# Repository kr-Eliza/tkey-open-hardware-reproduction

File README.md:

<p align="center">
<picture>
  <source media="(prefers-color-scheme: light)" srcset=".github/assets/banner-light.svg">
  
</picture>
</p>

<p align="center">
  <i>Can a student team rebuild an open hardware security key from its public sources, make it work, and understand what it takes to trust it?</i><br>
  We reproduced the <a href="https://tillitis.se">Tillitis TKey</a>: a 2-layer, hand-solderable redesign of its PCB, assembled in the lab and brought up until it behaved like a standard TKey.
</p>

<p align="center"><sub>Student project at my engineering school's LabCyber, team of six, November 2025 to April 2026 (<a href="https://ptcc.fr/lab-cyber/les-projets-du-labcyber/reproduction-dune-cle-dauthentification-open-hardware/">project page on the LabCyber site</a>). The project <a href="https://ptcc.fr/lab-cyber/les-projets-du-labcyber/projets-etudiants-au-labcyber/">continues at the LabCyber in 2026-2027</a>.</sub></p>

<p align="center">
<picture>
  <source media="(prefers-color-scheme: light)" srcset=".github/assets/divider-light.svg">
  
</picture>
</p>

<p align="center">
<picture>
  <source media="(prefers-color-scheme: light)" srcset=".github/assets/stats-light.svg">
  
</picture>
</p>

<h3>
<picture>
  <source media="(prefers-color-scheme: light)" srcset=".github/assets/h-why-this-project-light.svg">
  
</picture>
</h3>

Most hardware security keys are closed: their schematics, firmware and key storage cannot be inspected, so users have to trust the vendor. The TKey takes the opposite approach. Its hardware (a Lattice iCE40UP5K FPGA running a small RISC-V core, plus a CH552 USB controller) and its firmware are fully open, which makes it a good subject for a reproduction and hardening project:

- **reproduce** a real security device from its open sources, with the tools and constraints of a school lab;
- **understand** how it generates and protects its secrets;
- **propose** ways to strengthen it, and document everything as reusable material for the LabCyber.

**My part**, with one teammate: the custom PCB route, from the KiCad redesign to the order, the assembly and the bring-up of the board. The other members worked on the reference key, the Voltera prototype, the security analysis and the project management.

<h3>
<picture>
  <source media="(prefers-color-scheme: light)" srcset=".github/assets/h-three-routes-to-a-tkey-light.svg">
  
</picture>
</h3>

<p align="center">
<picture>
  <source media="(prefers-color-scheme: light)" srcset=".github/assets/journey-light.svg">
  
</picture>
</p>

| Route | What it is | Outcome |
|-------|-----------|---------|
| Reference key | a pre-assembled TKey Unlocked from Tillitis, provisioned by us | provisioned and used for signing, SSH and login MFA |
| Custom PCB | our 2-layer redesign, ordered from a PCB maker, assembled in the lab | assembled, powered and brought up until it behaved like a standard TKey |
| Voltera V-One | the same design printed in house with conductive ink | traces printed, assembly stopped (wrong consumables) |

<h3>
<picture>
  <source media="(prefers-color-scheme: light)" srcset=".github/assets/h-the-reference-tkey-light.svg">
  
</picture>
</h3>

The TKey Unlocked ships with a blank FPGA: no bitstream, no Unique Device Secret (UDS). We provisioned it ourselves from the `TK1-24.03` release of [tillitis-key1](https://github.com/tillitis/tillitis-key1):

1. **secrets**: the Tillitis provisioning tool derives the UDS from user entropy and 256 random bytes (HKDF);
2. **bitstream**: Yosys (synthesis), nextpnr-ice40 (place and route), the RISC-V cross-compiler for the firmware, icepack, about 102 KB in the end;
3. **flashing**: `tillitis-iceprog` through the TP-1 programmer, read back with `VERIFY OK`, then the UDS files were deleted from disk.

The provisioned key was then used for three things:

- **file signing** with `tkey-sign` (Ed25519), the key waiting for a physical touch before signing;
- **SSH** with `tkey-ssh-agent`, from Windows and Linux, no password, impossible once the key is unplugged;
- **two-factor login** on a Linux desktop: PAM asks for the password and a TKey challenge-response at the LightDM greeter.

<h3>
<picture>
  <source media="(prefers-color-scheme: light)" srcset=".github/assets/h-redesigning-the-pcb-light.svg">
  
</picture>
</h3>

The original TKey is a tiny 4-layer board with 0402 parts. We redesigned it in KiCad 9 for what a school lab can build and solder by hand.

| | Original TK1 | Our version |
|---|---|---|
| Layers | 4 | 2 |
| Board | USB stick | 57.6 x 39.8 mm card |
| Passives | 0402 / 0603 | 0805 |
| SPI flash | W25Q80 (USON-8) | SST25VF080B (SOIC-8) |
| USB connector | USB-A plug | USB-C receptacle (GCT USB4085) |
| Status LED | one RGB LED | three discrete 0805 LEDs |
| User input | capacitive touch sensor | push button on the same `TOUCH_EVENT` signal |
| Flash `WP#` / `HOLD#` | tied to fixed levels | routed to spare FPGA pins, so firmware can control write protection |
| Regulators | parts no longer available | NCP752 (3.3 V), MCP1824 (2.5 V), NCV8164 (1.2 V) |

Going from 4 to 2 layers removes the internal ground and power planes, so we had to work around it:

- copper ground pours on both layers, stitched with vias, to rebuild an approximate ground plane;
- decoupling capacitors as close as possible to every power pin, especially around the FPGA and the CH552;
- the USB D+ / D- pair kept short, tightly coupled and surrounded by ground, since a true 90 Ω impedance is hard to guarantee without a reference plane.

<table>
  <tr>
    <td></td>
    <td></td>
  </tr>
  <tr>
    <td align="center"><sub>front copper</sub></td>
    <td align="center"><sub>back copper</sub></td>
  </tr>
</table>

The 20 test points of the original are kept on the back (SPI, UART, GPIO and every supply rail), which is what made the bring-up possible.

The full bill of materials is in [`hardware/tk1-2layer/bom.csv`](hardware/tk1-2layer/bom.csv) and the schematic in [`docs/schematic-2layer.pdf`](docs/schematic-2layer.pdf).

<h3>
<picture>
  <source media="(prefers-color-scheme: light)" srcset=".github/assets/h-assembly-and-bring-up-light.svg">
  
</picture>
</h3>

The boards were made by an external PCB maker (2-layer FR4, 1.6 mm) and assembled in the lab: stencil and lead-free solder paste, pick-and-place for the passives, reflow oven, then inspection under the microscope. Two LEDs had been placed backwards and one CH552 pad lacked solder: all three were reworked by hand.

<table>
  <tr>
    <td width="33%"></td>
    <td width="33%"></td>
    <td width="33%"></td>
  </tr>
  <tr>
    <td align="center"><sub>assembled</sub></td>
    <td align="center"><sub>powered</sub></td>
    <td align="center"><sub>wired to the test points</sub></td>
  </tr>
</table>

**First power-on**, through a current-limited supply (100 mA): the 2.5 V, 1.2 V and 3.3 V rails were all within ±2 % of their targets, with about 15 mA drawn at idle and no short.

**Bring-up** was the hardest part. The board enumerated on Linux as `/dev/ttyACM0`, but `tkey-sign` failed with `GetAppNameVersion: ReadFrame: Read timeout`.

<p align="center">
<picture>
  <source media="(prefers-color-scheme: light)" srcset=".github/assets/bringup-light.svg">
  
</picture>
</p>

- Reflashing the official FPGA image through the TP-1 passed verification but did not change anything.
- The fix was on the **CH552 USB controller**: we rebuilt its firmware with `sdcc`, flashed it with `chprog`, and entered its bootloader by hand with a 10 kΩ pull-up on D+, since we had no dedicated reset adapter.
- From then on, the reproduced board behaved like a standard TKey.

<h3>
<picture>
  <source media="(prefers-color-scheme: light)" srcset=".github/assets/h-voltera-prototype-light.svg">
  
</picture>
</h3>

In parallel, another part of the team printed the design in house with a Voltera V-One: silver conductive ink for the traces, a drilling head and rivets for the vias, then solder paste and reflow on the heated bed. A board takes about an hour, which makes it a good tool to check a routing or a footprint quickly.

<table>
  <tr>
    <td width="45%"></td>
    <td width="55%"></td>
  </tr>
  <tr>
    <td align="center"><sub>printed board</sub></td>
    <td align="center"><sub>layout adapted for the printer</sub></td>
  </tr>
</table>

The traces printed well, but the assembly was stopped: the cartridge and nozzle available were not the right ones for solder paste. With the 0.5 mm pitch of the FPGA, the paste deposits would also have needed careful tuning to avoid bridges. Our conclusion: very good for testing, not for producing this board.

<h3>
<picture>
  <source media="(prefers-color-scheme: light)" srcset=".github/assets/h-supply-chain-light.svg">
  
</picture>
</h3>

A security key is only as trustworthy as the way it is built, so we started documenting the software supply chain, in [`supply-chain/`](supply-chain):

- [`sbom.cdx.json`](supply-chain/sbom.cdx.json): a CycloneDX 1.6 SBOM of the `tillitis-key1` sources, generated with syft (287 components);
- [`pbom.json`](supply-chain/pbom.json): the build provenance of the CH552 firmware (source commit, `tkey-builder` toolchain image, build command, SHA-256 of the produced `.hex` and `.bin`);
- [`hashes.txt`](supply-chain/hashes.txt): the same hashes, so anyone can rebuild the firmware and compare.

Built FPGA images are **not** published here: a TKey bitstream built for SPI flash can embed the device secrets (UDS), so it should never leave the bench it was made on.

<h3>
<picture>
  <source media="(prefers-color-scheme: light)" srcset=".github/assets/h-security-proposals-light.svg">
  
</picture>
</h3>

These are proposals only. For lack of time within the project, they could not be studied in depth: none of them was implemented in firmware or tested, and the reflection would need to go further before any of them is applied.

- **Memory isolation.** We studied a published out-of-bounds read in the TKey application RAM (a time-of-check to time-of-use bug on the size of the message to sign). Tillitis fixed it in the `TK1-24.03` hardware release, which is the one we built.
- **Post-quantum signatures.** Ed25519 would not resist a large quantum computer. We proposed a hybrid scheme, Ed25519 plus ML-DSA (FIPS 204), so a signature stays valid as long as one of the two holds.
- **Flash write protection.** Routing `WP#` and `HOLD#` to the FPGA gives the firmware a way to lock the flash, which the original board does not offer. The pins are routed on our board, but no firmware uses them yet.

The redesign also has a cost for security, worth keeping in mind for a hardened version: a larger board, exposed test points and a flash in a package that is easy to probe or swap are all easier to attack than the original stick. This is fine for a lab and teaching board, not for a key carried in a pocket.

<h3>
<picture>
  <source media="(prefers-color-scheme: light)" srcset=".github/assets/h-repository-light.svg">
  
</picture>
</h3>

```
hardware/
  tk1-2layer/          final 2-layer board sent to fabrication (KiCad 9 project, libraries, 3D models, BOM)
  voltera-prototype/   last version adapted for the Voltera V-One
docs/
  schematic-2layer.pdf
  images/              photos, KiCad renders, demo GIFs
supply-chain/          SBOM, build provenance and hashes of the CH552 firmware
```

Open `hardware/tk1-2layer/tk1-0805.kicad_pro` in KiCad 9. Only the last version of each board is kept; the FPGA design and firmware are the unmodified ones from [tillitis-key1](https://github.com/tillitis/tillitis-key1).

<h3>
<picture>
  <source media="(prefers-color-scheme: light)" srcset=".github/assets/h-limits-and-next-steps-light.svg">
  
</picture>
</h3>

- The USB signal quality on 2 layers was not measured; the board works, but its margin is unknown.
- Long-term reliability and repeatability over several boards remain to be tested.
- The reproduced board is programmed through its SPI flash, the development path: it is not locked like a production key (NVCM).
- The Voltera assembly still has to be validated with the right consumables.
- The security proposals are only first ideas: time ran out before they could be studied in depth, implemented in firmware or tested. This is where the 2026-2027 LabCyber project picks up (see below).

<h3>
<picture>
  <source media="(prefers-color-scheme: light)" srcset=".github/assets/h-the-project-continues-light.svg">
  
</picture>
</h3>

Our project is presented on the LabCyber site: [Reproduction d'une clé d'authentification open hardware](https://ptcc.fr/lab-cyber/les-projets-du-labcyber/reproduction-dune-cle-dauthentification-open-hardware/).

This work goes on at the LabCyber in 2026-2027, as one of its [student projects](https://ptcc.fr/lab-cyber/les-projets-du-labcyber/projets-etudiants-au-labcyber/): *reproduction and hardening of an open hardware device for authentication or data storage*, with the TKey and WooKey-type devices as examples. It starts where we stopped: understand the device, rebuild it from its open sources, harden it (firmware, manufacturing chain, attestation), and publish the results as commons that anyone can reuse.

**About the LabCyber.** The [LabCyber](https://ptcc.fr/lab-cyber/) is a shared lab of the Campus Cyber, operated by Inria within the [PTCC](https://ptcc.fr/programme-de-transfert-au-campus-cyber/qui-sommes-nous/) (Programme de Transfert au Campus Cyber, funded by France 2030). It brings together a fab lab, a cyber range and a data hub, hosts student teams for end-of-studies projects in hardware cybersecurity, and hosted this project. Its equipment includes:

- PCB fabrication and assembly: milling machine, reflow oven, soldering and hot-air stations, PCB microscope;
- electronics analysis: oscilloscope, logic analyzer, function generator, Faraday cage, software-defined radio;
- a cyber range to simulate IT and OT systems, and a contribution to the *Studio des Communs de la cybersécurité*.

<h3>
<picture>
  <source media="(prefers-color-scheme: light)" srcset=".github/assets/h-credits-and-license-light.svg">
  
</picture>
</h3>

Team of six engineering students, mentored at the LabCyber by two members of the PTCC, including [@Acathla-fr](https://github.com/Acathla-fr), who also helped finalize the files sent to fabrication. Original TKey design by [Tillitis AB](https://github.com/tillitis/tk1-pcba).

This is a modified version of the TK1 PCB by Tillitis AB, distributed under the same licence, the **CERN Open Hardware Licence Version 2, Strongly Reciprocal**. See [LICENSE.txt](LICENSE.txt).

```
Copyright Tillitis AB 2022-2024.
Modifications copyright 2026 the Open TKey student team.
This source describes Open Hardware and is licensed under the CERN-OHL-S v2.
You may redistribute and modify this source and make products using it under
the terms of the CERN-OHL-S v2 (https://ohwr.org/cern_ohl_s_v2.txt).
This source is distributed WITHOUT ANY EXPRESS OR IMPLIED WARRANTY,
INCLUDING OF MERCHANTABILITY, SATISFACTORY QUALITY AND FITNESS FOR A
PARTICULAR PURPOSE. Please see the CERN-OHL-S v2 for applicable conditions.
Source location: https://github.com/kr-Eliza/tkey-open-hardware-reproduction
Original source location: https://github.com/tillitis/tk1-pcba
Modified in 2026: 2-layer board, 0805 passives, SOIC-8 flash, USB-C connector,
discrete LEDs, push button, flash WP#/HOLD# routed to the FPGA, replacement
regulators (see "Redesigning the PCB" above).
```

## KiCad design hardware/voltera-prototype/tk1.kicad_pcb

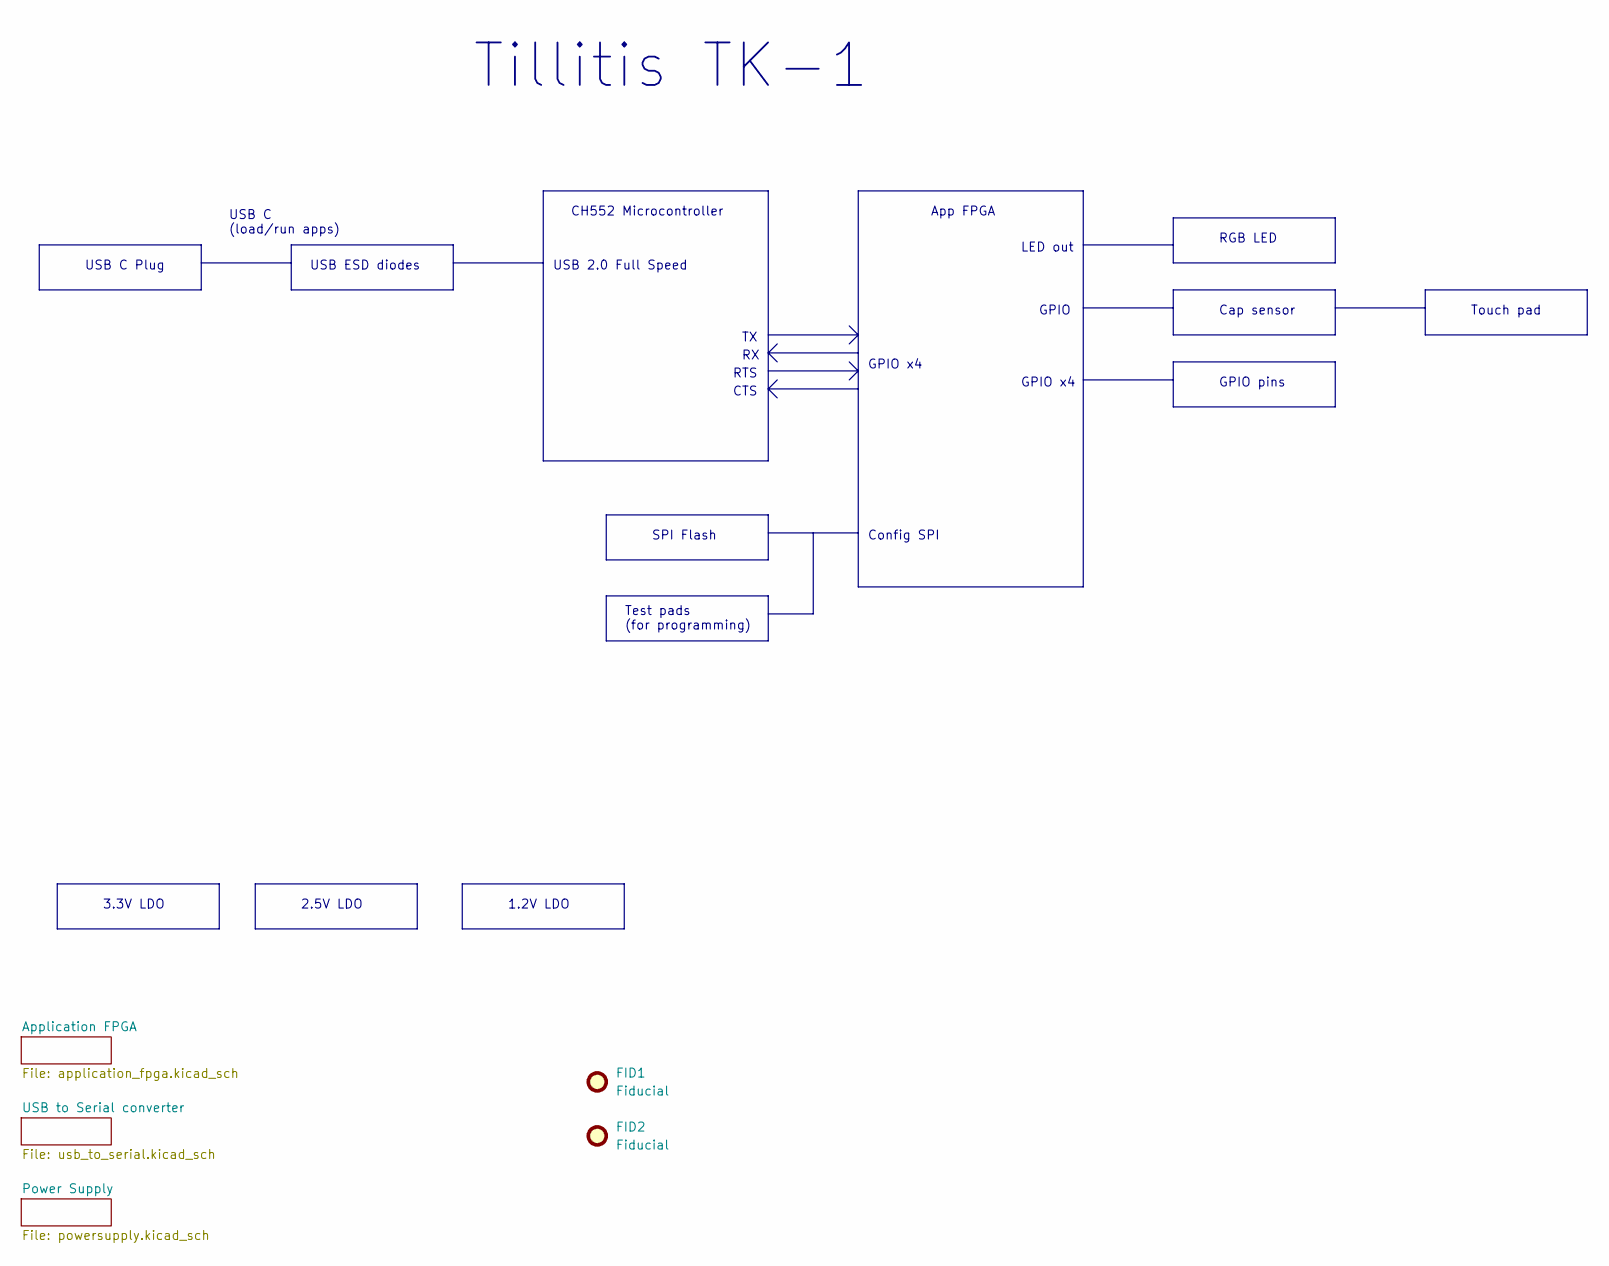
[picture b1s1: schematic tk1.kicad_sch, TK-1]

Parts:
FID1, FID2: Fiducial; Fiducial_0.75mm_Mask1.5mm

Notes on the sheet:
USB ESD diodes
Touch pad
GPIO x4
GPIO pins
Cap sensor
USB 2.0 Full Speed
RTS
USB C Plug
CH552 Microcontroller
RGB LED
USB C (load/run apps)
1.2V LDO
3.3V LDO
CTS
2.5V LDO
App FPGA
Config SPI
Tillitis TK-1
SPI Flash
GPIO
LED out
Test pads (for programming)

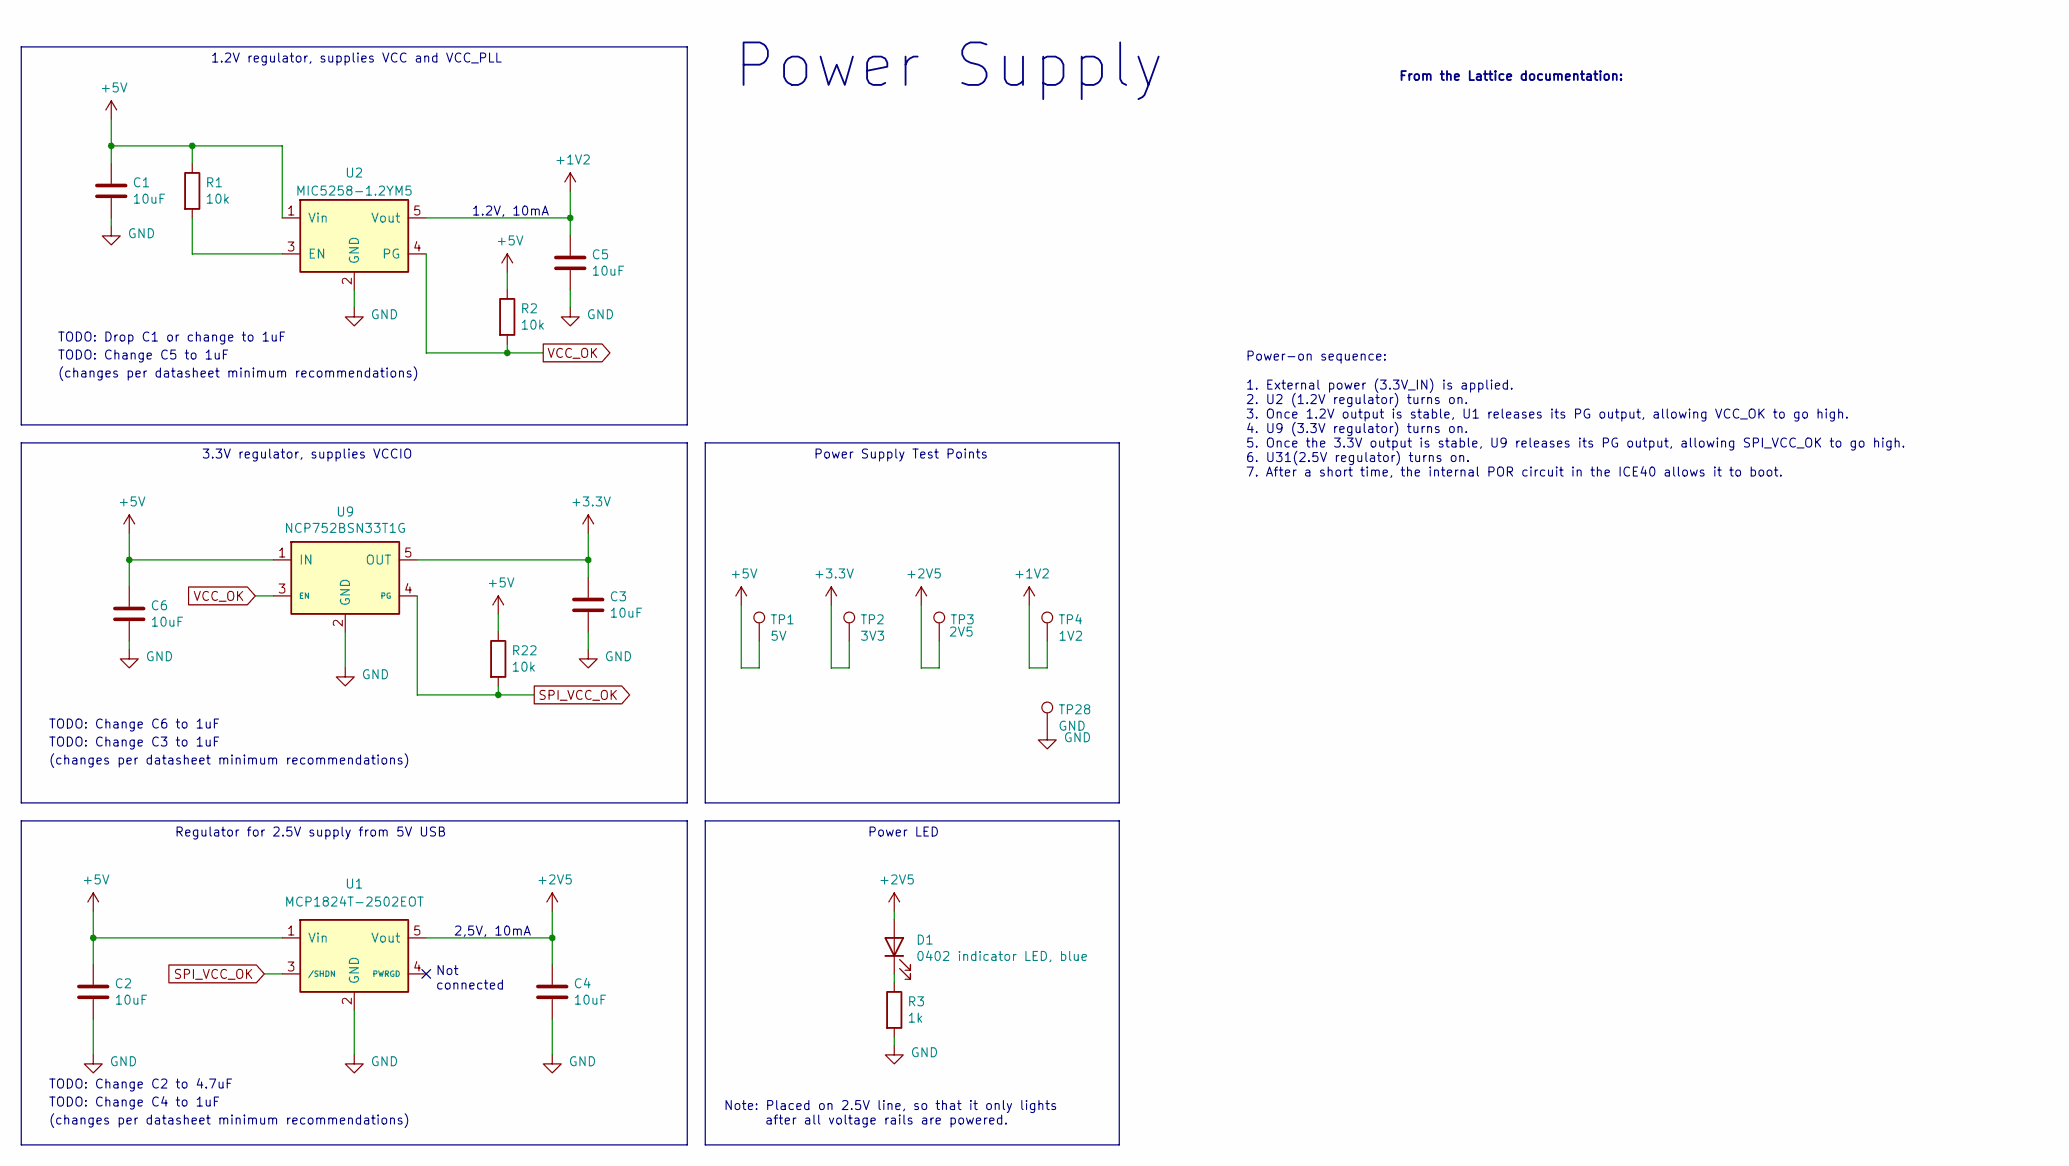
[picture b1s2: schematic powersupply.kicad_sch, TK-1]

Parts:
C1, C2, C3, C4, C5, C6: 10uF; C_0805_2012Metric
D1: 0402 indicator LED, blue; LED_0805_2012Metric; Manufacturer Part Number NCD0402B1
R1, R2, R22: 10k; R_0805_2012Metric
R3: 1k; R_0805_2012Metric
TP1: 5V; TestPoint_Pad_D1.0mm
TP2: 3V3; TestPoint_Pad_D1.0mm
TP3: 2V5; TestPoint_Pad_D1.0mm
TP4: 1V2; TestPoint_Pad_D1.0mm
TP28: GND; TestPoint_Pad_D1.0mm
U1: MCP1824T-2502EOT; SOT-23-5; Manufacturer Part Number MCP1824T-2502EOT
U2: MIC5258-1.2YM5; SOT-23-5; Manufacturer Part Number MIC5258-1.2YM5
U9: NCP752BSN33T1G; Manufacturer Part Number NCP752BSN33T1G

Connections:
+1V2: C5.1, TP4.1, U2.5 (Vout); also elsewhere on the board
+2V5: C4.1, D1.2 (A), TP3.1, U1.5 (Vout); also elsewhere on the board
+3.3V: C3.1, TP2.1, U9.5 (OUT); also elsewhere on the board
+5V: C1.1, C2.1, C6.1, R1.1, R2.1, R22.1, TP1.1, U1.1 (Vin), U2.1 (Vin), U9.1 (IN); also elsewhere on the board
GND: C1.2, C2.2, C3.2, C4.2, C5.2, C6.2, R3.2, TP28.1, U1.2 (GND), U2.2 (GND), U9.2 (GND); also elsewhere on the board
unnamed: D1.1 (K), R3.1
unnamed: R1.2, U2.3 (EN)
SPI_VCC_OK: R22.2, U1.3 (/SHDN), U9.4 (PG)
VCC_OK: R2.2, U2.4 (PG), U9.3 (EN)

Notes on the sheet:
Power-on sequence: 1. External power (3.3V_IN) is applied. 2. U2 (1.2V regulator) turns on. 3. Once 1.2V output is stable, U1 releases its PG output, allowing VCC_OK to go high. 4. U9 (3.3V regulator) turns on. 5. Once the 3.3V output is stable, U9 releases its PG output, allowing SPI_VCC_OK to go 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
TODO: Change C2 to 4.7uF
(changes per datasheet minimum recommendations)
TODO: Change C6 to 1uF
2,5V, 10mA
Note: Placed on 2.5V line, so that it only lights after all voltage rails are powered.
TODO: Change C3 to 1uF
1.2V, 10mA
Power Supply
TODO: Drop C1 or change to 1uF
TODO: Change C5 to 1uF
From the Lattice documentation:
1.2V regulator, supplies VCC and VCC_PLL
3.3V regulator, supplies VCCIO
TODO: Change C4 to 1uF
Not connected
Power Supply Test Points
Power LED
Regulator for 2.5V supply from 5V USB

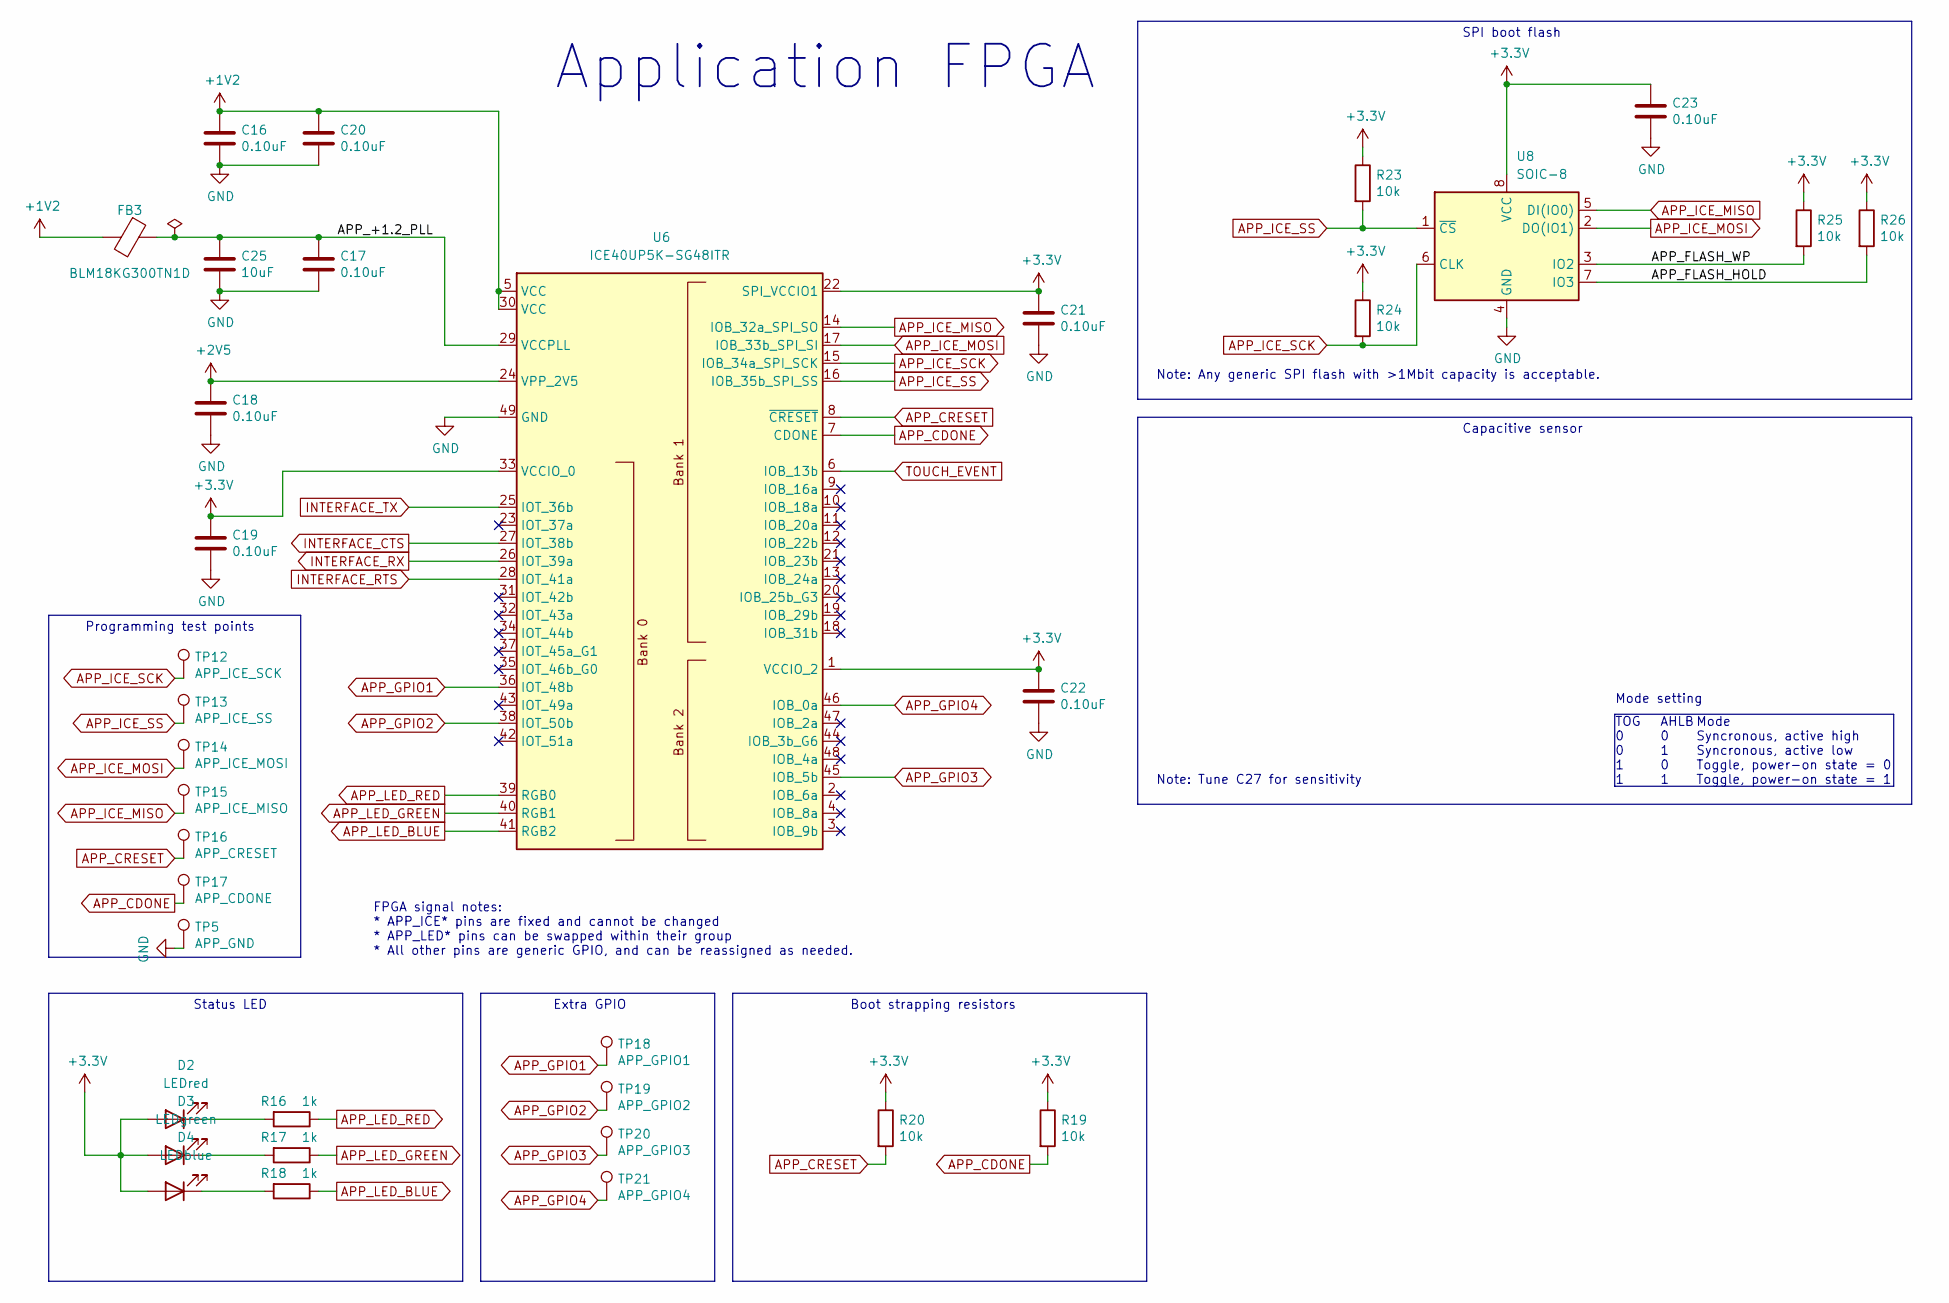
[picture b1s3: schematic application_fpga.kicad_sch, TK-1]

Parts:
C16, C17, C18, C19, C20, C21, C22, C23: 0.10uF; C_0805_2012Metric
C25: 10uF; C_0805_2012Metric
D2: LEDred; LED_0805_2012Metric_Pad1.15x1.40mm_HandSolder
D3: LEDgreen; LED_0805_2012Metric_Pad1.15x1.40mm_HandSolder
D4: LEDblue; LED_0805_2012Metric_Pad1.15x1.40mm_HandSolder
FB3: BLM18KG300TN1D; Ferritbead_0603_1608Metric; Manufacturer Part Number BLM18KG300TN1D
R16, R17, R18: 1k; R_0805_2012Metric
R19, R20, R23, R24, R25, R26: 10k; R_0805_2012Metric
TP5: APP_GND; TestPoint_Pad_D1.0mm
TP12: APP_ICE_SCK; TestPoint_Pad_D1.0mm
TP13: APP_ICE_SS; TestPoint_Pad_D1.0mm
TP14: APP_ICE_MOSI; TestPoint_Pad_D1.0mm
TP15: APP_ICE_MISO; TestPoint_Pad_D1.0mm
TP16: APP_CRESET; TestPoint_Pad_D1.0mm
TP17: APP_CDONE; TestPoint_Pad_D1.0mm
TP18: APP_GPIO1; TestPoint_Pad_D1.0mm
TP19: APP_GPIO2; TestPoint_Pad_D1.0mm
TP20: APP_GPIO3; TestPoint_Pad_D1.0mm
TP21: APP_GPIO4; TestPoint_Pad_D1.0mm
U6: ICE40UP5K-SG48ITR; QFN-48-1EP_7x7mm_P0.5mm_EP5.6x5.6mm; Manufacturer Part Number ICE40UP5K-SG48ITR
U8: SOIC-8; SOIC-8_3.9x4.9mm_P1.27mm; Manufacturer Part Number W25Q80DVUXIE

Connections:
+1V2: C16.1, C20.1, FB3.2, U6.5 (VCC), U6.30 (VCC); also elsewhere on the board
+2V5: C18.1, U6.24 (VPP_2V5); also elsewhere on the board
+3.3V: C19.1, C21.1, C22.1, C23.1, D2.2 (A), D3.2 (A), D4.2 (A), R19.1, R20.1, R23.1, R24.1, R25.1, R26.1, U6.1 (VCCIO_2), U6.22 (SPI_VCCIO1), U6.33 (VCCIO_0), U8.8 (VCC); also elsewhere on the board
/Application FPGA/APP_+1.2_PLL: C17.1, C25.1, FB3.1, U6.29 (VCCPLL)
/Application FPGA/APP_FLASH_HOLD: R26.2, U8.7 (IO3)
/Application FPGA/APP_FLASH_WP: R25.2, U8.3 (IO2)
APP_CDONE: R19.2, TP17.1, U6.7 (CDONE)
APP_CRESET: R20.2, TP16.1, U6.8 (~CRESET)
APP_GPIO1: TP18.1, U6.36 (IOT_48b)
APP_GPIO2: TP19.1, U6.38 (IOT_50b)
APP_GPIO3: TP20.1, U6.45 (IOB_5b)
APP_GPIO4: TP21.1, U6.46 (IOB_0a)
APP_ICE_MISO: TP15.1, U6.14 (IOB_32a_SPI_SO), U8.5 (DI(IO0))
APP_ICE_MOSI: TP14.1, U6.17 (IOB_33b_SPI_SI), U8.2 (DO(IO1))
APP_ICE_SCK: R24.2, TP12.1, U6.15 (IOB_34a_SPI_SCK), U8.6 (CLK)
APP_ICE_SS: R23.2, TP13.1, U6.16 (IOB_35b_SPI_SS), U8.1 (~CS)
APP_LED_BLUE: R18.1, U6.41 (RGB2)
APP_LED_GREEN: R17.1, U6.40 (RGB1)
APP_LED_RED: R16.1, U6.39 (RGB0)
GND: C16.2, C17.2, C18.2, C19.2, C20.2, C21.2, C22.2, C23.2, C25.2, TP5.1, U6.49 (GND), U8.4 (GND); also elsewhere on the board
INTERFACE_CTS: U6.27 (IOT_38b); also elsewhere on the board
INTERFACE_RTS: U6.28 (IOT_41a); also elsewhere on the board
INTERFACE_RX: U6.26 (IOT_39a); also elsewhere on the board
INTERFACE_TX: U6.25 (IOT_36b); also elsewhere on the board
unnamed: D3.1 (K), R17.2
TOUCH_EVENT: U6.6 (IOB_13b)

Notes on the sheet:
Application FPGA
Mode Syncronous, active high Syncronous, active low Toggle, power-on state = 0 Toggle, power-on state = 1
Capacitive sensor
SPI boot flash
FPGA signal notes: * APP_ICE* pins are fixed and cannot be changed * APP_LED* pins can be swapped within their group * All other pins are generic GPIO, and can be reassigned as needed.
Boot strapping resistors
AHLB 0 1 0 1
Status LED
Note: Tune C27 for sensitivity
Programming test points
Mode setting
Note: Any generic SPI flash with >1Mbit capacity is acceptable.
Extra GPIO
TOG 0 0 1 1

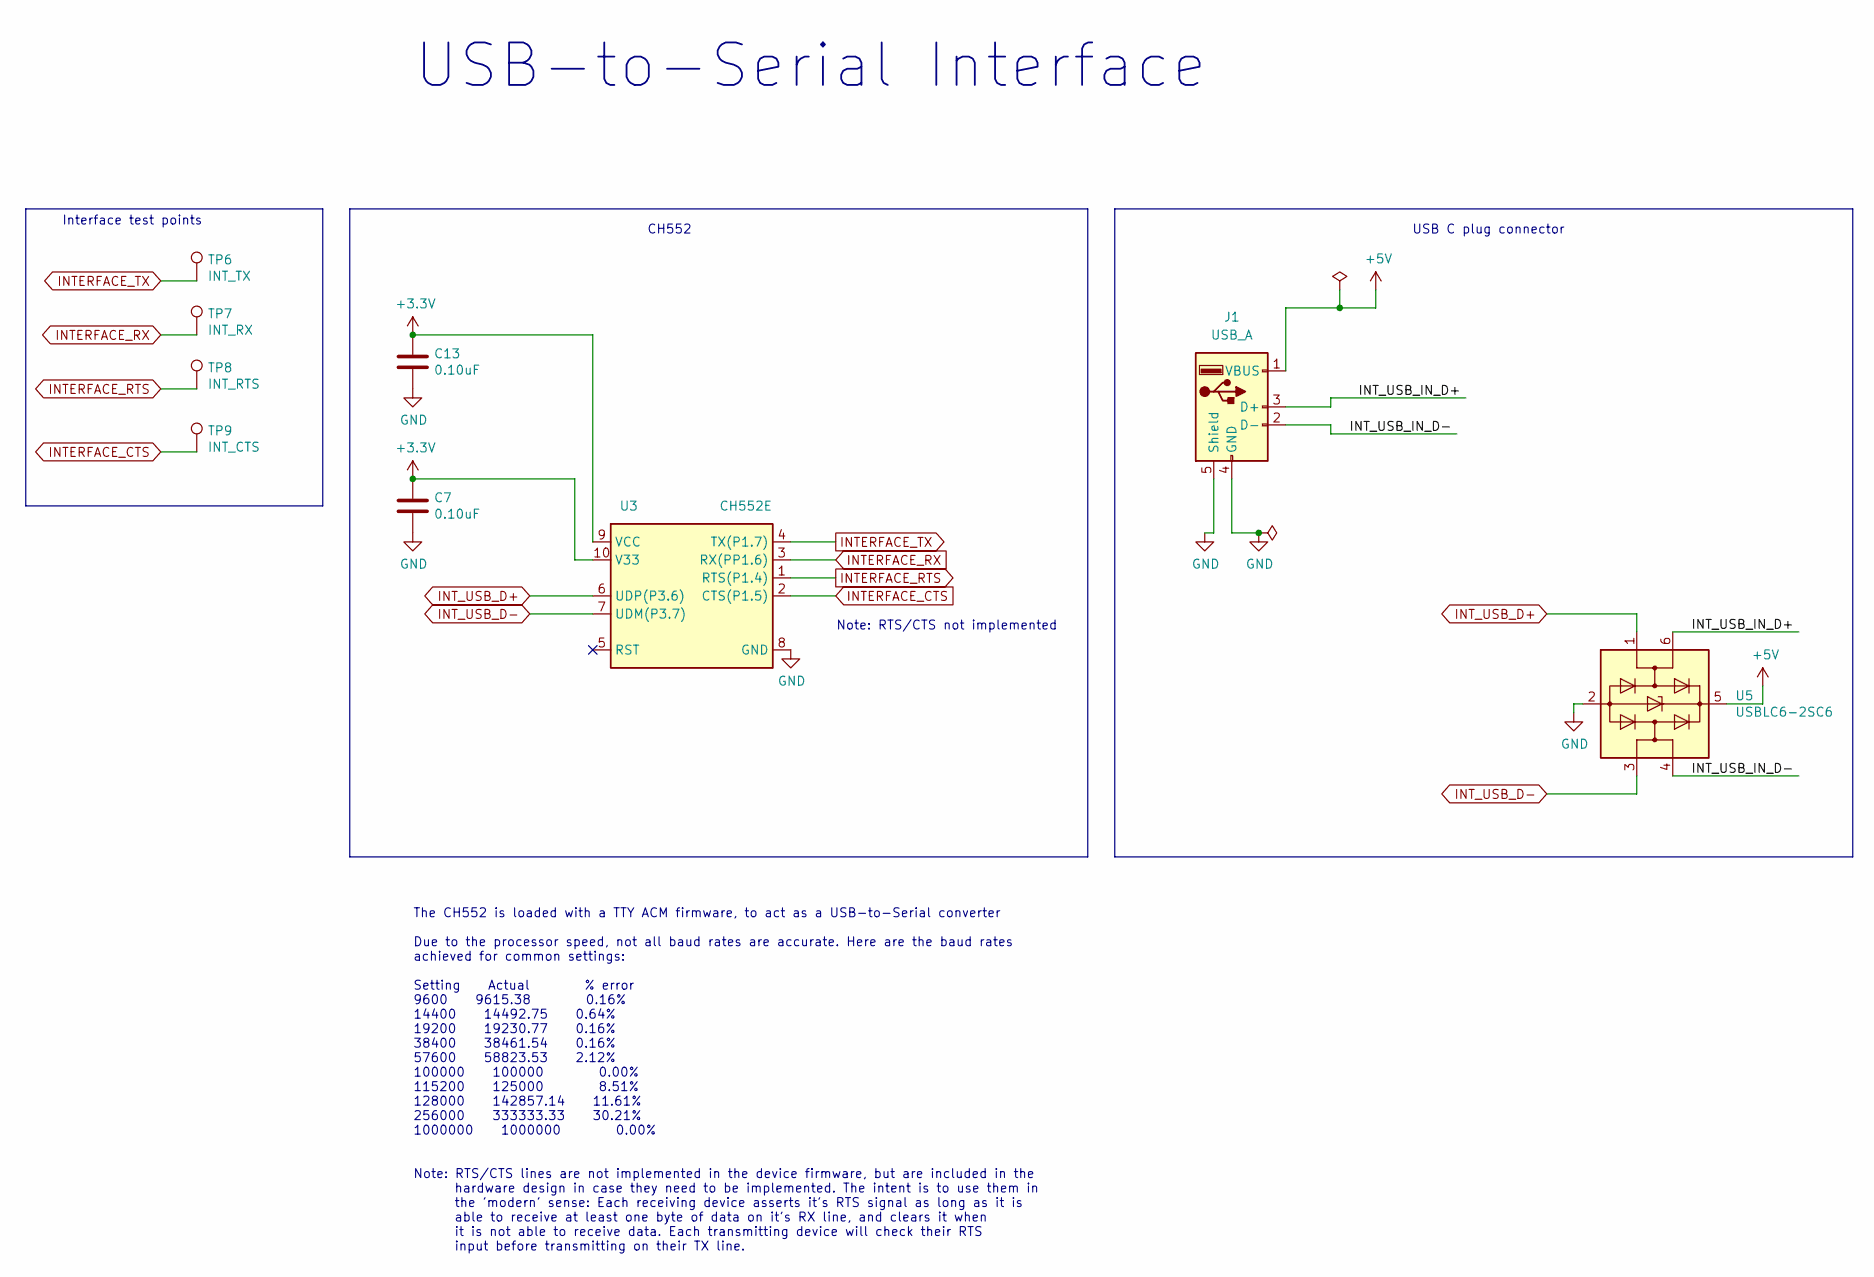
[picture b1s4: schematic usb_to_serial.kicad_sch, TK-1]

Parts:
C7, C13: 0.10uF; C_0805_2012Metric
J1: USB_A; USB_A_Kycon_KUSBX-AS1N-B_Horizontal
TP6: INT_TX; TestPoint_Pad_D1.0mm
TP7: INT_RX; TestPoint_Pad_D1.0mm
TP8: INT_RTS; TestPoint_Pad_D1.0mm
TP9: INT_CTS; TestPoint_Pad_D1.0mm
U3: CH552E; MSOP-10_3x3mm_P0.5mm; Manufacturer Part Number CH552E
U5: USBLC6-2SC6; SOT-23-6; Manufacturer Part Number USBLC6-2SC6

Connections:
+3.3V: C7.1, C13.1, U3.9 (VCC), U3.10 (V33); also elsewhere on the board
+5V: J1.1 (VBUS), U5.5 (VBUS); also elsewhere on the board
/USB to Serial converter/INT_USB_IN_D+: J1.3 (D+), U5.6 (I/O1)
/USB to Serial converter/INT_USB_IN_D-: J1.2 (D-), U5.4 (I/O2)
GND: C7.2, C13.2, J1.4 (GND), J1.5 (Shield), U3.8 (GND), U5.2 (GND); also elsewhere on the board
INTERFACE_CTS: TP9.1, U3.2 (CTS(P1.5)); also elsewhere on the board
INTERFACE_RTS: TP8.1, U3.1 (RTS(P1.4)); also elsewhere on the board
INTERFACE_RX: TP7.1, U3.3 (RX(PP1.6)); also elsewhere on the board
INTERFACE_TX: TP6.1, U3.4 (TX(P1.7)); also elsewhere on the board
INT_USB_D+: U3.6 (UDP(P3.6)), U5.1 (I/O1)
INT_USB_D-: U3.7 (UDM(P3.7)), U5.3 (I/O2)

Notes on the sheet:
USB C plug connector
CH552
USB-to-Serial Interface
The CH552 is loaded with a TTY ACM firmware, to act as a USB-to-Serial converter Due to the processor speed, not all baud rates are accurate. Here are the baud rates achieved for common settings: Setting Actual % error 9600 9615.38 0.16% 14400 14492.75 0.64% 19200 19230.77 0.16% 38400 38461.54 0.16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
Interface test points
Note: RTS/CTS not implemented

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
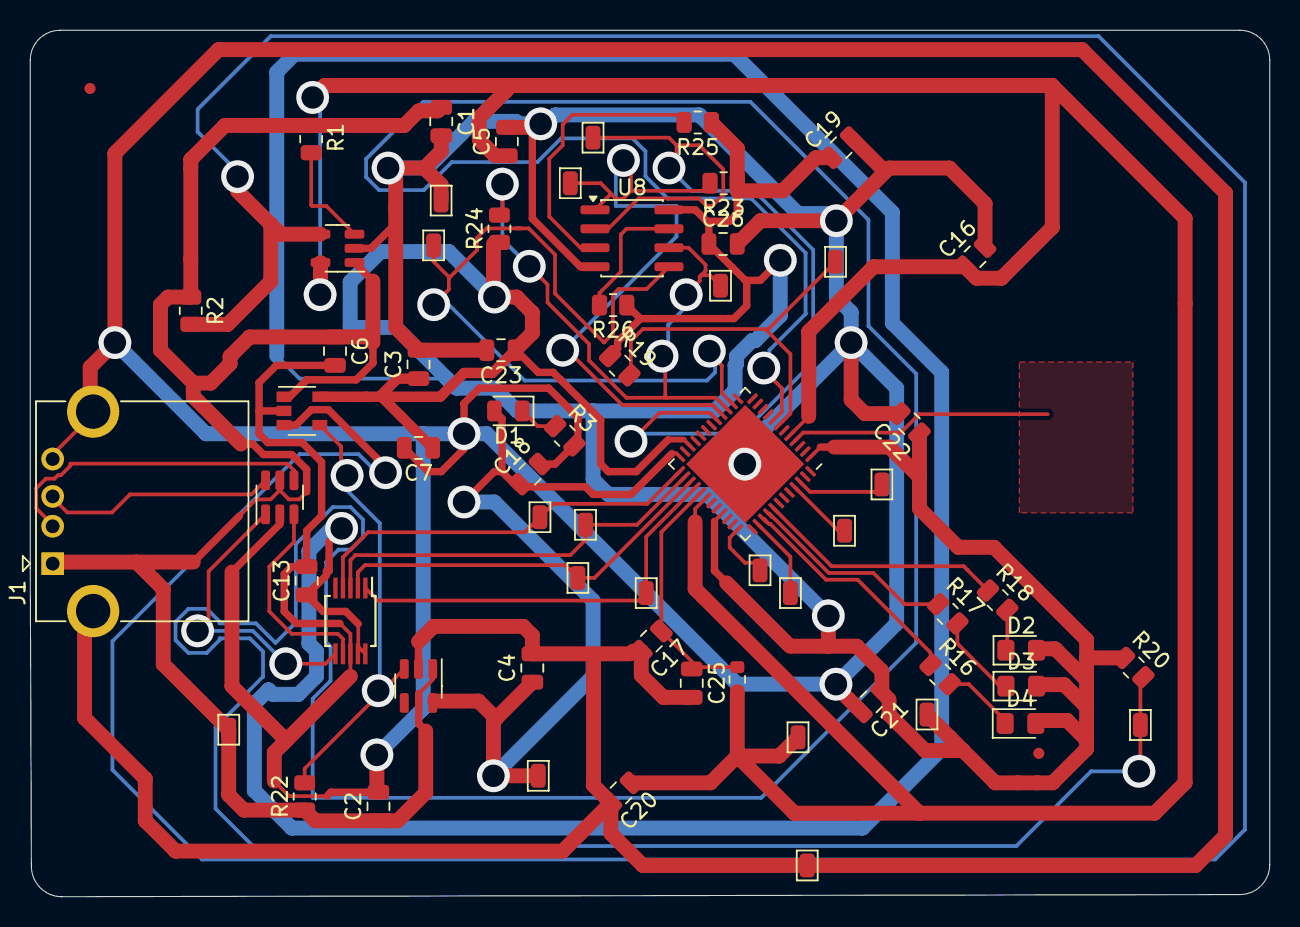
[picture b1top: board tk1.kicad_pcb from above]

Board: 2 copper layers, 83.0 x 58.0 mm, 66 parts (0 on the bottom side), 36 nets.

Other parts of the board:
C26: 0.10uF; C_0805_2012Metric

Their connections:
+3.3V: C26.1; also elsewhere on the board
GND: C26.2; also elsewhere on the board

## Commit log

2026-04-01 Open TKey: reproduction of the Tillitis TKey on a 2-layer hand-solderable PCB
